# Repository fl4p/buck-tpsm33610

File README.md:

# buck-tpsm33610

A 3–36 V to 3.3 V, 1 A break-out board for the TI **TPSM33610S3QRDNRQ1** — a
synchronous buck *module* with the controller, both FETs, the inductor and the
bootstrap capacitor inside one 3.5 × 4.5 × 2.1 mm QFN-FCMOD package.

**9.01 × 12.525 mm**, 2 layers, one 2.54 mm header row: VIN, GND, VOUT.

> **Status: unbuilt.** This board has never been fabricated, assembled or
> powered. No gerbers have been generated. Every number below is either a
> datasheet value or a computed estimate — none of it is a bench measurement.
> Treat it as a design under review, not a validated product.

## What is generated

Everything. The KiCad symbol, footprints, schematic and PCB are all outputs of
the Python in this repo; the `.kicad_sch` and `.kicad_pcb` are build artefacts
and hand edits in the GUI are overwritten on the next run.

```
variants.py           geometry constants -- the single source of truth
project_settings.py   owns .kicad_pro design rules; apply() / verify()
gen_sym.py         -> lib/buck-tpsm33610.kicad_sym
gen_fp.py          -> lib/buck-tpsm33610.pretty/*.kicad_mod
gen_sch.py         -> buck-tpsm33610.kicad_sch
gen_pcb.py         -> buck-tpsm33610.kicad_pcb   (placement, routing, pours, fill)
check_netlist.py      capture-completion gate
```

Regenerate, in order. `gen_pcb.py` needs KiCad's bundled interpreter, the only
one that can `import pcbnew`:

```sh
KI=/Applications/KiCad/KiCad.app/Contents
KIPY=$KI/Frameworks/Python.framework/Versions/Current/bin/python3
CLI=$KI/MacOS/kicad-cli

python3 gen_sym.py && python3 gen_fp.py && python3 gen_sch.py
$CLI sch erc --severity-all --exit-code-violations -o erc.rpt buck-tpsm33610.kicad_sch
$CLI sch export netlist -o buck-tpsm33610.net buck-tpsm33610.kicad_sch
$KIPY gen_pcb.py
$CLI pcb drc --severity-all --schematic-parity --exit-code-violations \
     -o drc.rpt buck-tpsm33610.kicad_pcb
```

Built and verified against KiCad 10.0.5.

Two flags matter more than they look. `--exit-code-violations` is not
decoration: without it `kicad-cli` writes the violations to the report and still
exits 0. And DRC is deliberately run **without** `--refill-zones` — re-pouring
from the project at check time grades a board that is not the one in the file,
and that is exactly how an isolated pad hid here once.

## Design

| | |
|---|---|
| Input | 3–36 V (40 V abs max), no reverse-polarity or transient protection |
| Output | 3.3 V fixed, 1 A, ±1 % |
| Switching | 2.2 MHz, auto/PFM by default (see DRSS note below) |
| Layers | 2 × 35 µm (1 oz), ENIG, 1.6 mm FR4 |
| Drawn to | 150 µm track / 150 µm clearance |
| I/O | one 1×3 header, 2.54 mm: VIN, GND, VOUT |
| Control | EN, PGOOD, MODE on 1.0 mm solder pads; JP1 selects FPWM |

Pin rules from TI **SNVSCS7E** that shape the whole layout: SW (5, 6) carries no
copper beyond its lands; BOOT (7) is a no-connect because the 100 nF is internal;
MODE/SYNC (11) has a **5.5 V abs max** and must never reach VIN; PGOOD (1) tops
out at 20 V, so its pull-up goes to VOUT. `gen_sch.py` asserts these as an
abs-max-per-pin gate at generation time, so a net that could over-volt a pin
fails the build rather than the board.

The datasheet states the 100 nF bootstrap cap is internal (p.5, pin 7) and
requires external bypass at VIN (p.5, pin 3). It does not say whether any
internal VIN bypass exists; assume none and bypass externally.

### Two layers

TI's datasheet asks for four. The cost is quantified rather than waived: on a
1.6 mm two-layer board the image plane sits 1.6 mm below F.Cu instead of ~0.2 mm,
so a top-side switching run encloses roughly 8× the area. What makes it
defensible is that the highest-di/dt loop is kept small locally and the back side
is one unbroken ground pour.

### Verification gates

The generators are gates, not reports — each fails the build:

- **Fill runs in a clean subprocess.** `CreateEmptyBoard()` loads KiCad's default
  project into the interpreter, and a later `LoadBoard()` in the same process
  keeps those defaults, so an in-process pour uses the wrong clearances. This
  cost a silently isolated pad once.
- **Connectivity after fill** — every pad must reach every other pad on its net,
  or the build fails.
- **Courtyard overlap by polygon intersection**, not inflated bounding boxes.
- **Abs-max per U1 pin** from the datasheet table.
- **BOM line consistency** — parts sharing an MPN must agree on value and footprint.
- **MODE never floats** in any jumper state.

## Known and open

- **Thermal is an estimate, not a measurement, and the estimate is unsourced.**
  ~120 °C/W at the 35 µm this board actually specifies, against TI's 54.1 °C/W
  JESD 51-7 four-layer figure and 22 °C/W for their EVM. No derivation for that
  number exists in this repo — treat it as an order-of-magnitude expectation, not
  a bounded estimate. That predicts full 1 A to roughly 80 °C ambient at
  24 V and ~64 °C at 36 V. Unverified. ΨJB is 16.3 °C/W, so the acceptance test
  is to probe board temperature beside the GND land and compute
  `Tj = Tboard + 16.3 × Pd`.
- **Input loop inductance: 3.67 nH of board copper** (C1‖C2), extracted with
  FastHenry at 0.25 mm mesh pitch, ±1 % over a 2.5× pitch range. This is **board
  copper only and a lower bound** — the module's pad-to-die path is not published
  and is deliberately not estimated. Not cross-checked against hardware. **The
  extraction tool is not in this repo** and neither is its output, so nothing here
  substantiates that figure; it is reproduced from an external run.
- **The VIN neck is 0.245 mm and is marginal at the specified copper weight.**
  At 35 µm, IPC-2221 gives **0.86 A at 10 K rise and 1.17 A at 20 K**. Worst-case
  input current is ~1.0–1.1 A, which occurs at the low end of the *regulating*
  input range (around 3.5–4 V, where duty is highest); below that the part is in
  dropout and no longer making 3.3 V. So the neck sits **above its 10 K rating and
  inside its 20 K rating** — it works, at a higher local rise than is comfortable.
  At 70 µm the same neck gives 1.43 A / 1.93 A and is unambiguously fine. TI asks
  for 2 oz outer layers (SNVSCS7E p.35 item 6); this board is drawn at 1 oz.
- **Resistance of the declared power paths** at 35 µm, 0.1 mm solver grid:
  `/VIN C1.1↔U1.3` 9.27 mΩ, `/VIN J1.1↔U1.3` 11.04, `GND J1.2↔U1.10` 3.23,
  `GND C2.2↔U1.10` 2.36, `/VOUT J1.3↔U1.4` 1.84, `/VOUT U1.4↔C4.1` 0.96.
- **Spread spectrum is mostly OFF in the shipped default.** Table 7-2 calls the
  MODE-low state "auto mode with spread spectrum", but §7.3.8 p.18 overrides it:
  DRSS is disabled whenever the clock is not free-running — including when the
  clock slows under light load in auto mode, and in dropout. Bridge JP1 for FPWM
  if you want DRSS active at light load.
- **Two accepted DRC warnings**: the C1–C4 courtyard overlap (side-by-side pair
  whose cheapest escape is X, not Y) and an R3/R6 silkscreen clearance. Zero
  errors, zero unconnected pads. The generators cite a `DESIGN.md` for the
  per-pair disposition of those warnings; **that file does not exist**, so the
  waiver is currently undocumented.
- **No input protection at all** — no TVS, no reverse-polarity FET, not even a
  DNP land. EN is hard-tied to VIN. Nothing here survives a hot-unplug inductive
  kick on a long 36 V lead. Bench use from a stiff supply only.
- `make_fab.py` is not written, so there are no gerbers and no assembly data.

## Datasheet

TI **SNVSCS7E**, "TPSM336xx-Q1". Not redistributed here —
`datasheets/PROVENANCE.md` carries the source URL and the SHA-256 of the exact
revision every page citation in this repo refers to.

## History

Developed inside a private monorepo; this repository starts from a squashed
snapshot, so the per-change history is not carried over.

## Licence

Not yet chosen, so no licence is granted — all rights reserved for now. If you
want to use any of this, open an issue and ask.

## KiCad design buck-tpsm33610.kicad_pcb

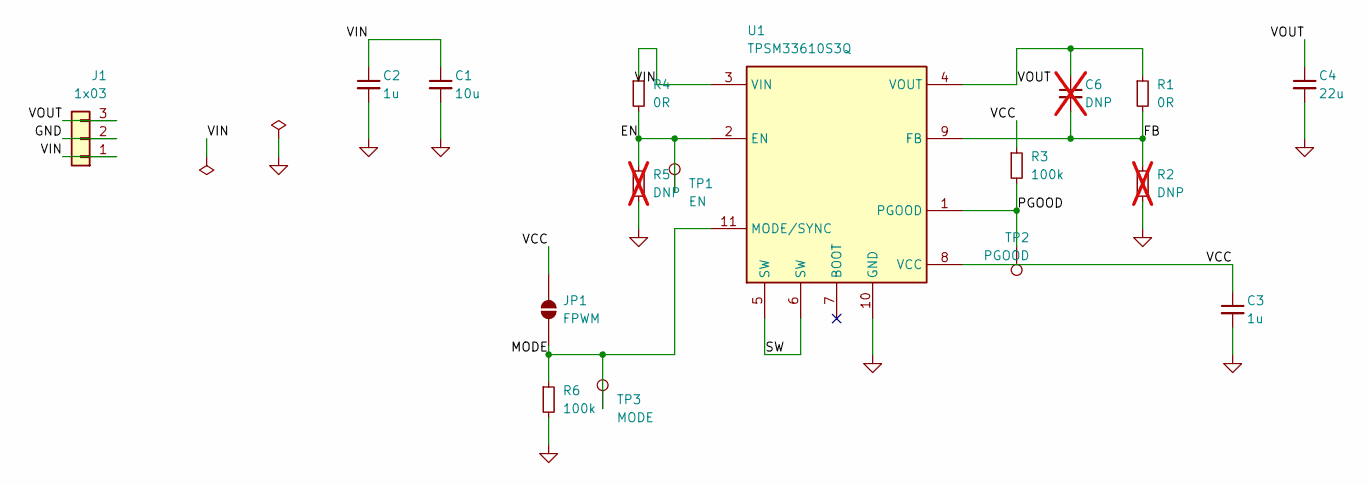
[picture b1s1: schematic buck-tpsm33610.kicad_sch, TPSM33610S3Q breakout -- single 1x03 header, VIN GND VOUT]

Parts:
C1: 10u; C_1206_3216Metric; MPN CGA5L1X7R1H106K160AC
C2, C3: 1u; C_0603_1608Metric; MPN CL10B105KB8NQNC
C4: 22u; C_1206_3216Metric; MPN EMK316BB7226ML-T
C6: DNP; C_0402_1005Metric; not fitted
J1: 1x03; PinHeader_1x03_P2.54mm_Vertical_NoSilk; MPN 61300311121
JP1: FPWM; SolderJumper_2_P1.00mm_Open_Pad0.8x0.4mm
R1, R4: 0R; R_0402_1005Metric; MPN RC0402JR-070RL
R2, R5: DNP; R_0402_1005Metric; not fitted
R3, R6: 100k; R_0402_1005Metric; MPN RC0402FR-07100KL
TP1: EN; TestPad_1.0x1.0mm
TP2: PGOOD; TestPad_1.0x1.0mm
TP3: MODE; TestPad_1.0x1.0mm
U1: TPSM33610S3Q; TPSM336xx_QFN-FCMOD-11_RDN0011B_TI; MPN TPSM33610S3QRDNRQ1

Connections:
/EN: R4.2, R5.1, TP1.1, U1.2 (EN)
/FB: C6.2, R1.2, R2.1, U1.9 (FB)
/MODE: JP1.2 (B), R6.1, TP3.1, U1.11 (MODE/SYNC)
/PGOOD: R3.2, TP2.1, U1.1 (PGOOD)
/SW: U1.5 (SW), U1.6 (SW)
/VCC: C3.1, JP1.1 (A), R3.1, U1.8 (VCC)
/VIN: C1.1, C2.1, J1.1, R4.1, U1.3 (VIN)
/VOUT: C4.1, C6.1, J1.3, R1.1, U1.4 (VOUT)
GND: C1.2, C2.2, C3.2, C4.2, J1.2, R2.2, R5.2, R6.2, U1.10 (GND)

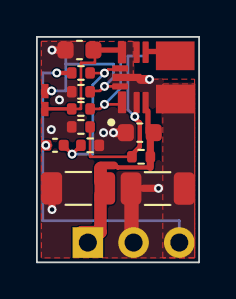
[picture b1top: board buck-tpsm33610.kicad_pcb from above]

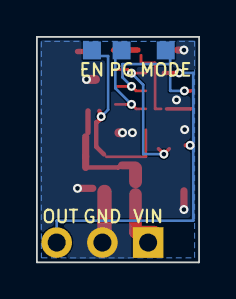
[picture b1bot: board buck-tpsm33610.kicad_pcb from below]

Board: 2 copper layers, 9.0 x 12.5 mm, 17 parts (3 on the bottom side), 9 nets.
